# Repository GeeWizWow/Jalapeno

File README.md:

# Jalapeno BLE

## References

* [Raytac MDBT40 spec sheet](http://www.raytac.com/download/MDBT40/MDBT40%20spec-Version%20A7.pdf)
* [Adafruit feather 32u4 schematic](https://cdn-learn.adafruit.com/assets/assets/000/028/668/original/adafruit_products_schem.png?1447886222)
* [KLE Layout](http://www.keyboard-layout-editor.com/#/gists/c4e9117bac25465440a420f333e7f61a)
* [Adafruit NRF51822 Flasher](https://github.com/adafruit/Adafruit_nRF51822_Flasher)
* [Render KLE](https://github.com/CQCumbers/kle_render)

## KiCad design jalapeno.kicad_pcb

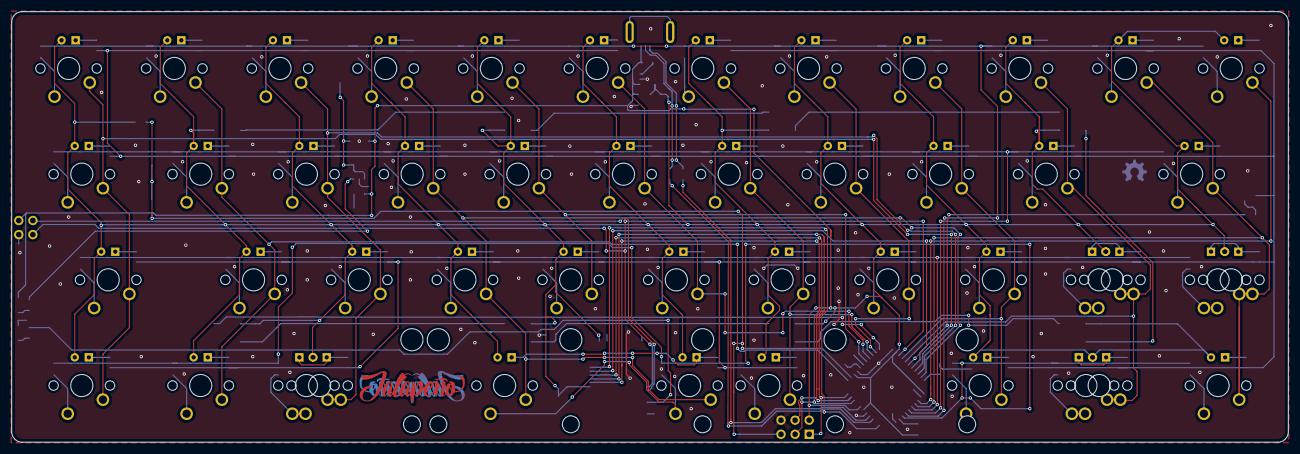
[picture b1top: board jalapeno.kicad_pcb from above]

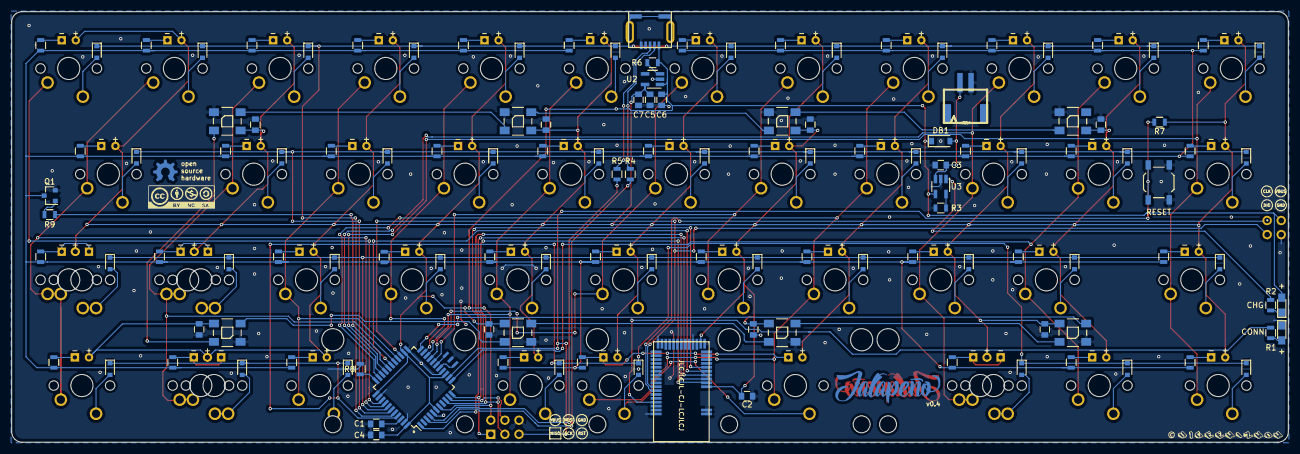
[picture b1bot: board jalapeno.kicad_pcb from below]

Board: 2 copper layers, 230.1 x 77.6 mm, 187 parts (134 on the bottom side), 137 nets.

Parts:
C1, C2, C7: 1uF; C_0805
C3, C5, C6: 10µF; C_0805
C4: 10uF; C_0805
CR1, CR2, CR3, CR4, CR5, CR6, CR7, CR8: 0.1uf; C_0805
D1, D2, D3, D4, D5, D6, D7, D8, D9, D10, D11, D12, D13, D14, D15, D16, D17, D18, D19, D20, D21, D22, D23, D24, D25, D26, D27, D28, D29, D30, D31, D32, D33, D34, D35, D36, D37, D38, D39, D40, D41, D42: D; D_0805
DB1: MBR120; D_SOD-123
G1: Logo; LOGO
G1_0: Logo Front; LOGO
G2: OSHW logo; OSHW_Logo
G3: CC logo; CC-BY-NC-SA
G4: Copyright; COPYRIGHT
H1, H2, H3, H4, H6: Mounting_Hole; NOOP
IC1: ATMEGA32U4-AU; TQFP-44_10x10mm_Pitch0.8mm
J1: USB_B; USB_miniB_hirose_5S8
J2: AVR-ISP-6; AVR_ICSP_3x2_NO_SILK
J3: Conn_01x04; AVR_2x2_NO_SILK
JST1: JST_BAT; JST-PH-2
K1: esc; CHERRY_PCB_100H_LED
K2: q; CHERRY_PCB_100H_LED
K3: w; CHERRY_PCB_100H_LED
K4: e; CHERRY_PCB_100H_LED
K5: r; CHERRY_PCB_100H_LED
K6: t; CHERRY_PCB_100H_LED
K7: y; CHERRY_PCB_100H_LED
K8: u; CHERRY_PCB_100H_LED
K9: i; CHERRY_PCB_100H_LED
K10: o; CHERRY_PCB_100H_LED
K11: p; CHERRY_PCB_100H_LED
K12: back; CHERRY_PCB_100H_LED
K13: tab; CHERRY_PCB_125H_LED
K14: a; CHERRY_PCB_100H_LED
K15: s; CHERRY_PCB_100H_LED
K16: d; CHERRY_PCB_100H_LED
K17: f; CHERRY_PCB_100H_LED
K18: g; CHERRY_PCB_100H_LED
K19: h; CHERRY_PCB_100H_LED
K20: j; CHERRY_PCB_100H_LED
K21: k; CHERRY_PCB_100H_LED
K22: l; CHERRY_PCB_100H_LED
K23: ;; CHERRY_PCB_175H_LED
K24: caps; CHERRY_PCB_175H_LED
K25: caps; CHERRY_PCB_100H_LED
K26: z; CHERRY_PCB_100H_LED
K27: x; CHERRY_PCB_100H_LED
K28: c; CHERRY_PCB_100H_LED
K29: v; CHERRY_PCB_100H_LED
K30: b; CHERRY_PCB_100H_LED
K31: n; CHERRY_PCB_100H_LED
K32: m; CHERRY_PCB_100H_LED
K33: ,; CHERRY_PCB_125H_LED
K33_1: ,; CHERRY_PCB_100H_LED_REVERSED
K34: .; CHERRY_PCB_100H_LED
K34_1: .; CHERRY_PCB_125H_LED_REVERSED
K35, K41: ctrl; CHERRY_PCB_125H_LED
K36, K39_1: gui; CHERRY_PCB_100H_LED
K37: alt; CHERRY_PCB_100H_LED_REVERSED
K37_1: alt; CHERRY_PCB_125H_LED
K38: space; CHERRY_PCB_625H_LED
K38_1: space; CHERRY_PCB_225H_LED
K39: alt; CHERRY_PCB_125H_LED_REVERSED
K40: gui; CHERRY_PCB_125H_LED
K42: KEYSW; CHERRY_PCB_275H_LED
LED1, LED2, LED3, LED4, LED5, LED6, LED7, LED8: WS2812B
LED1_0: CHG; LED_0805_HandSoldering
LED2_0: CONN; LED_0805_HandSoldering
Q1: MMBT2222ALT3G; SOT-23
R1: 2.2k; R_0805
R2: 1k; R_0805
R3, R7, R8: 10k; R_0805
R4, R5: 22ohm; R_0805
R6: 100k; R_0805
R9: 1.5k; R_0805
RK1, RK2, RK4, RK5, RK6, RK7, RK8, RK9, RK10, RK11, RK12, RK13, RK14, RK15, RK16, RK17, RK18, RK19, RK20, RK21, RK22, RK23, RK24, RK25, RK26, RK27, RK28, RK29, RK30, RK31, RK32, RK33, RK34, RK35, RK36, RK37, RK38, RK39, RK40, RK41, RK42: 330; R_0805
Rk3: 330; R_0805
SW1: SW_PUSH; SW_SPST_TL3342
U1: MDBT40
U2: SPX3819M5-L-3-3; SOT-23-5_HandSoldering
U3: MCP73831T-2ACI/OT; SOT-23-5_HandSoldering
Y1: XTAL_GND; smd_resonator_3pin_3x1.2mm

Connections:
+3V3: C2.2, C4.2, C5.1, C7.1, CR1.2, CR2.2, CR3.2, CR4.2, CR5.2, CR6.2, CR7.2, CR8.2, IC1.6, IC1.14, IC1.24, IC1.34, IC1.44, K1.3, K2.3, K3.3, K4.3, K5.3, K6.3, K7.3, K8.3, K9.3, K10.3, K11.3, K12.3, K13.3, K14.3, K15.3, K16.3, K17.3, K18.3, K19.3, K20.3, K21.3, K22.3, K23.3, K24.3, K25.3, K26.3, K27.3, K28.3, K29.3, K30.3, K31.3, K32.3, K33.3, K33_1.3, K34.3, K34_1.3, K35.3, K36.3, K37.3, K37_1.3, K38.3, K38_1.3, K39.3, K39_1.3, K40.3, K41.3, K42.3, LED1.1, LED2.1, LED3.1, LED4.1, LED5.1, LED6.1, LED7.1, LED8.1, R7.1, U1.3, U1.14, U2.5
+BATT: C3.1, DB1.2, JST1.1, U3.3
/4_SWDIO/RST: IC1.25, J3.4, U1.35
/7_BLE_IRQ: IC1.1, U1.8
/8_BLE_CS: IC1.28, U1.7
/AREF: C1.1, IC1.42
/MISO: IC1.11, J2.1, U1.5
/MOSI: IC1.10, J2.4, U1.6
/RESET: IC1.13, J2.5, R7.2, SW1.2
/SCK: IC1.9, J2.3, U1.4
/SWDCLK: J3.3, U1.36
COL_1: IC1.30, K1.2, K13.2, K24.2, K35.2
COL_2: IC1.12, K2.2, K14.2, K25.2, K36.2
COL_3: IC1.31, K3.2, K15.2, K26.2, K37.2, K37_1.2
COL_4: IC1.32, K4.2, K16.2, K27.2, K38.2, K38_1.2
COL_5: IC1.18, K5.2, K17.2, K28.2
COL_6: IC1.19, K6.2, K18.2, K29.2
COL_7: IC1.20, K7.2, K19.2, K30.2, K42.2
COL_8: IC1.21, K8.2, K20.2, K31.2
COL_9: IC1.26, K9.2, K21.2, K32.2, K41.2
COL_10: IC1.27, K10.2, K22.2, K33.2, K33_1.2, K39.2, K39_1.2
COL_11: IC1.37, K11.2, K23.2, K34.2, K34_1.2, K40.2
COL_12: IC1.36, K12.2
GND: C1.2, C2.1, C3.2, C4.1, C5.2, C6.2, C7.2, CR1.1, CR2.1, CR3.1, CR4.1, CR5.1, CR6.1, CR7.1, CR8.1, IC1.5, IC1.15, IC1.23, IC1.35, IC1.43, J1.5, J2.6, J3.2, JST1.2, LED1.3, LED2.3, LED2_0.1, LED3.3, LED4.3, LED5.3, LED6.3, LED7.3, LED8.3, Q1.2, R3.1, R8.2, SW1.1, U1.1, U1.2, U1.13, U1.16, U1.25, U1.42, U2.2, U3.2, Y1.3
LEDGND: Q1.3, RK1.2, RK2.2, RK4.2, RK5.2, RK6.2, RK7.2, RK8.2, RK9.2, RK10.2, RK11.2, RK12.2, RK13.2, RK14.2, RK15.2, RK16.2, RK17.2, RK18.2, RK19.2, RK20.2, RK21.2, RK22.2, RK23.2, RK24.2, RK25.2, RK26.2, RK27.2, RK28.2, RK29.2, RK30.2, RK31.2, RK32.2, RK33.2, RK34.2, RK35.2, RK36.2, RK37.2, RK38.2, RK39.2, RK40.2, RK41.2, RK42.2, Rk3.2
LEDPWM: IC1.29, R9.2
unnamed: D1.2, K1.1
unnamed: D2.2, K2.1
unnamed: D3.2, K3.1
unnamed: D4.2, K4.1
unnamed: D5.2, K5.1
unnamed: D6.2, K6.1
unnamed: D7.2, K7.1
unnamed: D8.2, K8.1
unnamed: D9.2, K9.1
unnamed: D10.2, K10.1
unnamed: D11.2, K11.1
unnamed: D12.2, K12.1
unnamed: D13.2, K13.1
unnamed: D14.2, K14.1
unnamed: D15.2, K15.1
unnamed: D16.2, K16.1
unnamed: D17.2, K17.1
unnamed: D18.2, K18.1
unnamed: D19.2, K19.1
unnamed: D20.2, K20.1
unnamed: D21.2, K21.1
unnamed: D22.2, K22.1
unnamed: D23.2, K23.1
unnamed: D24.2, K24.1
unnamed: D25.2, K25.1
unnamed: D26.2, K26.1
unnamed: D27.2, K27.1
unnamed: D28.2, K28.1
unnamed: D29.2, K29.1
unnamed: D30.2, K30.1
unnamed: D31.2, K31.1
unnamed: D32.2, K32.1
unnamed: D33.2, K33.1, K33_1.1
unnamed: D34.2, K34.1, K34_1.1
unnamed: D35.2, K35.1
unnamed: D36.2, K36.1
unnamed: D37.2, K37.1, K37_1.1
unnamed: D38.2, K38.1, K38_1.1
unnamed: D39.2, K39.1, K39_1.1
unnamed: D40.2, K40.1
unnamed: D41.2, K41.1
unnamed: D42.2, K42.1
unnamed: IC1.3, R4.2
unnamed: IC1.4, R5.2
unnamed: IC1.16, Y1.1
unnamed: IC1.17, Y1.2
unnamed: IC1.33, R8.1
unnamed: J1.2, R4.1
unnamed: J1.3, R5.1
unnamed: K1.4, RK1.1
unnamed: K2.4, RK2.1
unnamed: K3.4, Rk3.1
unnamed: K4.4, RK4.1
unnamed: K5.4, RK5.1
unnamed: K6.4, RK6.1
unnamed: K7.4, RK7.1
unnamed: K8.4, RK8.1
unnamed: K9.4, RK9.1
unnamed: K10.4, RK10.1
unnamed: K11.4, RK11.1
unnamed: K12.4, RK12.1
unnamed: K13.4, RK13.1
unnamed: K14.4, RK14.1
unnamed: K15.4, RK15.1
unnamed: K16.4, RK16.1
unnamed: K17.4, RK17.1
unnamed: K18.4, RK18.1
unnamed: K19.4, RK19.1
unnamed: K20.4, RK20.1
unnamed: K21.4, RK21.1
unnamed: K22.4, RK22.1
unnamed: K23.4, RK23.1
unnamed: K24.4, RK24.1
unnamed: K25.4, RK25.1
unnamed: K26.4, RK26.1
unnamed: K27.4, RK27.1
unnamed: K28.4, RK28.1
unnamed: K29.4, RK29.1
unnamed: K30.4, RK30.1
unnamed: K31.4, RK31.1
unnamed: K32.4, RK32.1
unnamed: K33.4, K33_1.4, RK33.1
unnamed: K34.4, K34_1.4, RK34.1
unnamed: K35.4, RK35.1
unnamed: K36.4, RK36.1
unnamed: K37.4, K37_1.4, RK37.1
unnamed: K38.4, K38_1.4, RK38.1
unnamed: K39.4, K39_1.4, RK39.1
unnamed: K40.4, RK40.1
unnamed: K41.4, RK41.1
unnamed: K42.4, RK42.1
unnamed: LED1.2, LED2.4
unnamed: LED1_0.1, R2.2
unnamed: LED2.2, LED3.4
unnamed: LED2_0.2, R1.1
unnamed: LED3.2, LED4.4
unnamed: LED4.2, LED5.4
unnamed: LED5.2, LED6.4
unnamed: LED6.2, LED7.4
unnamed: LED7.2, LED8.4
unnamed: Q1.1, R9.1
unnamed: R1.2, U1.39
unnamed: R2.1, U3.1
unnamed: R3.2, U3.5
unnamed: R6.1, U2.3
RGB: IC1.22, LED1.4
ROW_1: D1.1, D2.1, D3.1, D4.1, D5.1, D6.1, D7.1, D8.1, D9.1, D10.1, D11.1, D12.1, IC1.40
ROW_2: D13.1, D14.1, D15.1, D16.1, D17.1, D18.1, D19.1, D20.1, D21.1, D22.1, D23.1, IC1.39
ROW_3: D24.1, D25.1, D26.1, D27.1, D28.1, D29.1, D30.1, D31.1, D32.1, D33.1, D34.1, IC1.38
ROW_4: D35.1, D36.1, D37.1, D38.1, D39.1, D40.1, D41.1, D42.1, IC1.41
VBUS: C6.1, DB1.1, IC1.7, J1.1, J2.2, J3.1, LED1_0.2, R6.2, U2.1, U3.4

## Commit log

2018-05-20 initial
2018-05-20 added layout to readme
2018-05-20 readme - added references
2018-05-20 Create LICENSE
2018-05-20 added libs, redrew schematic and redid component association
2018-05-20 update crystal footprint + regenerated new netlist
2018-05-20 added new footprints
2018-05-21 started re-routing
2018-05-26 layout update
2018-05-26 updated readme links
2018-05-26 new renders
2018-05-26 updated renders
2018-05-26 readme new line
2018-05-27 new pcb & routing
2018-05-27 finished routing...
2018-05-28 new routing
2018-05-29 done routing
2018-05-29 new switch footprint
2018-05-30 gerber export & logo
2018-06-10 v0.3.0
2018-06-10 v0.3 renders
2018-06-15 logos
2018-06-15 rgb caps
2018-06-16 placed components
2018-06-23 routing + plate
2018-06-24 power routing
2018-06-24 plate
2018-06-24 routing stuck
2018-06-24 routing DRC + row 4
2018-06-25 plate mod
2018-06-26 routing finalised
2018-09-04 removed images
2018-09-04 qmk config
